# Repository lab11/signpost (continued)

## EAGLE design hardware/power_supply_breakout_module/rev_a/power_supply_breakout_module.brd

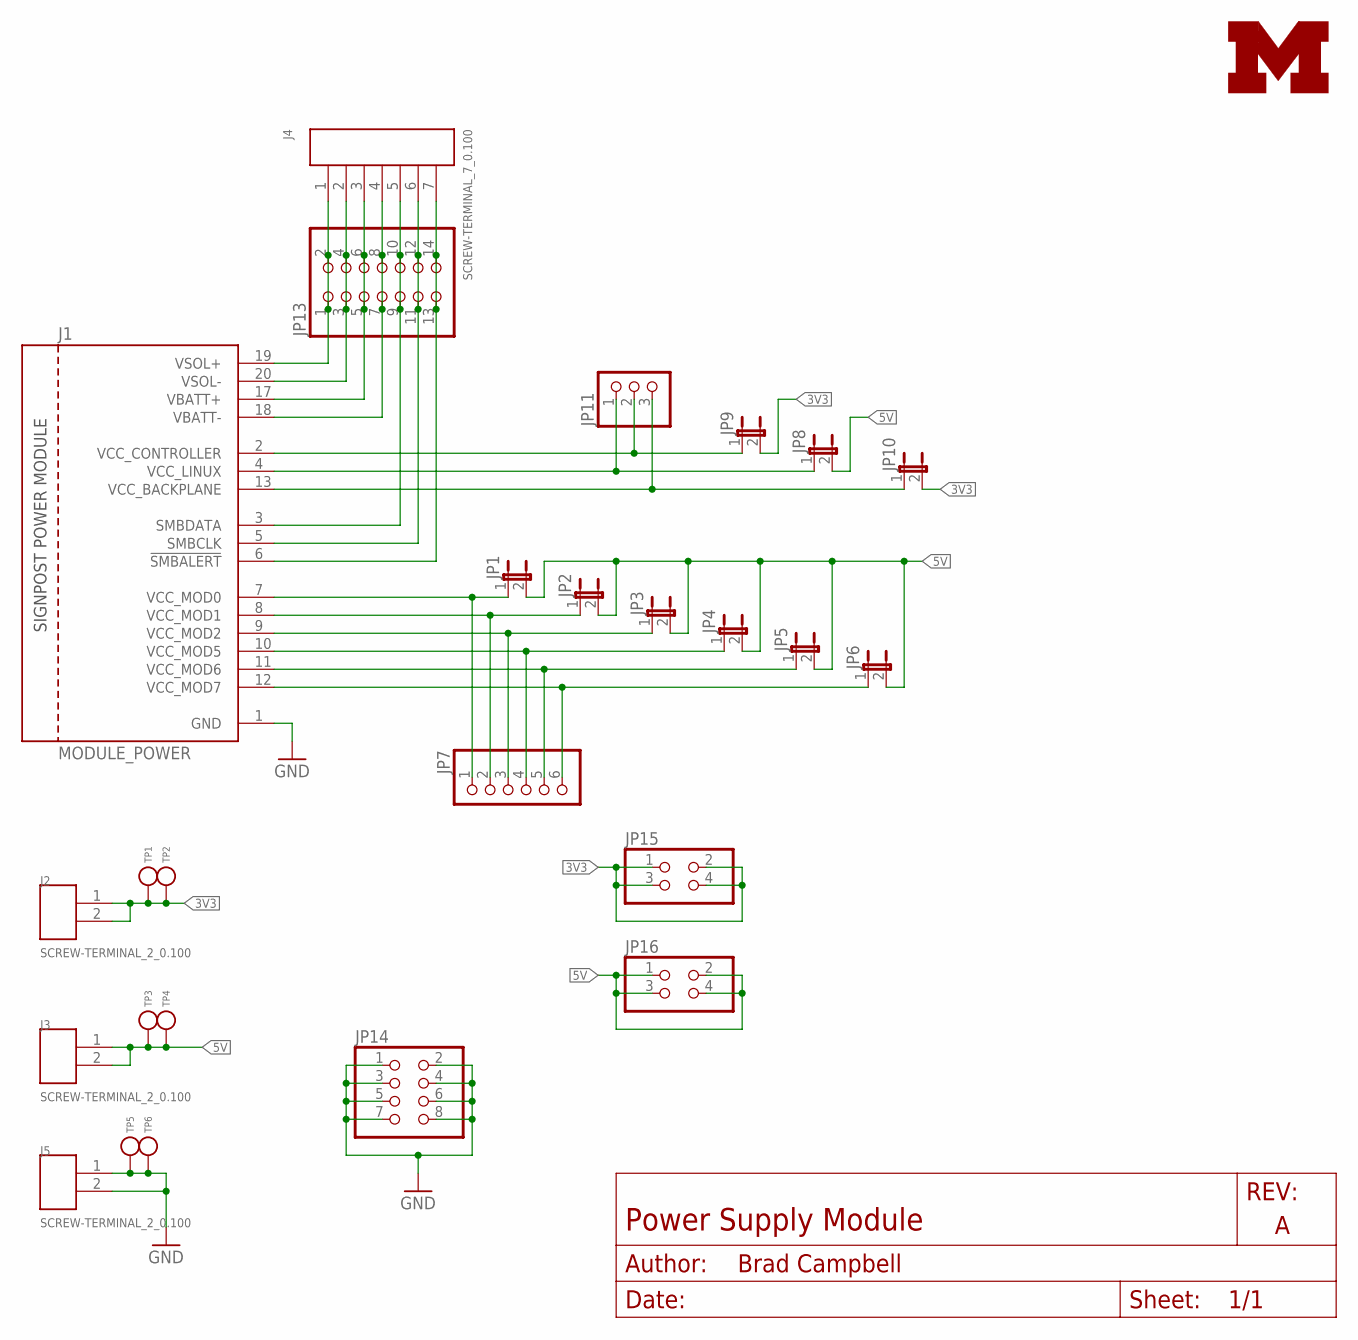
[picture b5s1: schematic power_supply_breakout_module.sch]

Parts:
J1: MODULE_POWER
J2, J3, J5: SCREW-TERMINAL_2_0.100; CONN_BLOCK_2
J4: SCREW-TERMINAL_7_0.100; CONN_BLOCK_7
JP1, JP2, JP3, JP4, JP5, JP6, JP8, JP9, JP10: JUMPER-2PTH; 1X02
JP7: PINHD-1X6; 1X06
JP11: PINHD-1X3; 1X03
JP13: PINHD-2X7; 2X07
JP14: PINHD-2X4; 2X04
JP15, JP16: PINHD-2X2; 2X02
LOGO1: UMICH_SOLID_MEDIUM; UMICH_SOLID_200MIL
TP1, TP2, TP3, TP4, TP5, TP6: TEST_POINT_0.040IN; TESTPOINT_0.040IN

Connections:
3V3: J2.1, J2.2, JP9.2, JP10.2, JP15.1, JP15.2, JP15.3, JP15.4, TP1.TESTPOINT, TP2.TESTPOINT
5V: J3.1, J3.2, JP1.2, JP2.2, JP3.2, JP4.2, JP5.2, JP6.2, JP8.2, JP16.1, JP16.2, JP16.3, JP16.4, TP3.TESTPOINT, TP4.TESTPOINT
!SMBALERT: J1.6 (!SMBALERT), J4.7, JP13.13, JP13.14
GND: J1.1 (GND), J5.1, J5.2, JP14.1, JP14.2, JP14.3, JP14.4, JP14.5, JP14.6, JP14.7, JP14.8, TP5.TESTPOINT, TP6.TESTPOINT
SMBCLK: J1.5 (SMBCLK), J4.6, JP13.11, JP13.12
SMBDATA: J1.3 (SMBDATA), J4.5, JP13.9, JP13.10
VBATT+: J1.17 (VBATT+), J4.3, JP13.5, JP13.6
VBATT-: J1.18 (VBATT-), J4.4, JP13.7, JP13.8
VCC_BACKPLANE: J1.13 (VCC_BACKPLANE), JP10.1, JP11.3
VCC_CONTROLLER: J1.2 (VCC_CONTROLLER), JP9.1, JP11.2
VCC_LINUX: J1.4 (VCC_LINUX), JP8.1, JP11.1
VCC_MOD0: J1.7 (VCC_MOD0), JP1.1, JP7.1
VCC_MOD1: J1.8 (VCC_MOD1), JP2.1, JP7.2
VCC_MOD2: J1.9 (VCC_MOD2), JP3.1, JP7.3
VCC_MOD5: J1.10 (VCC_MOD5), JP4.1, JP7.4
VCC_MOD6: J1.11 (VCC_MOD6), JP5.1, JP7.5
VCC_MOD7: J1.12 (VCC_MOD7), JP6.1, JP7.6
VSOL+: J1.19 (VSOL+), J4.1, JP13.1, JP13.2
VSOL-: J1.20 (VSOL-), J4.2, JP13.3, JP13.4

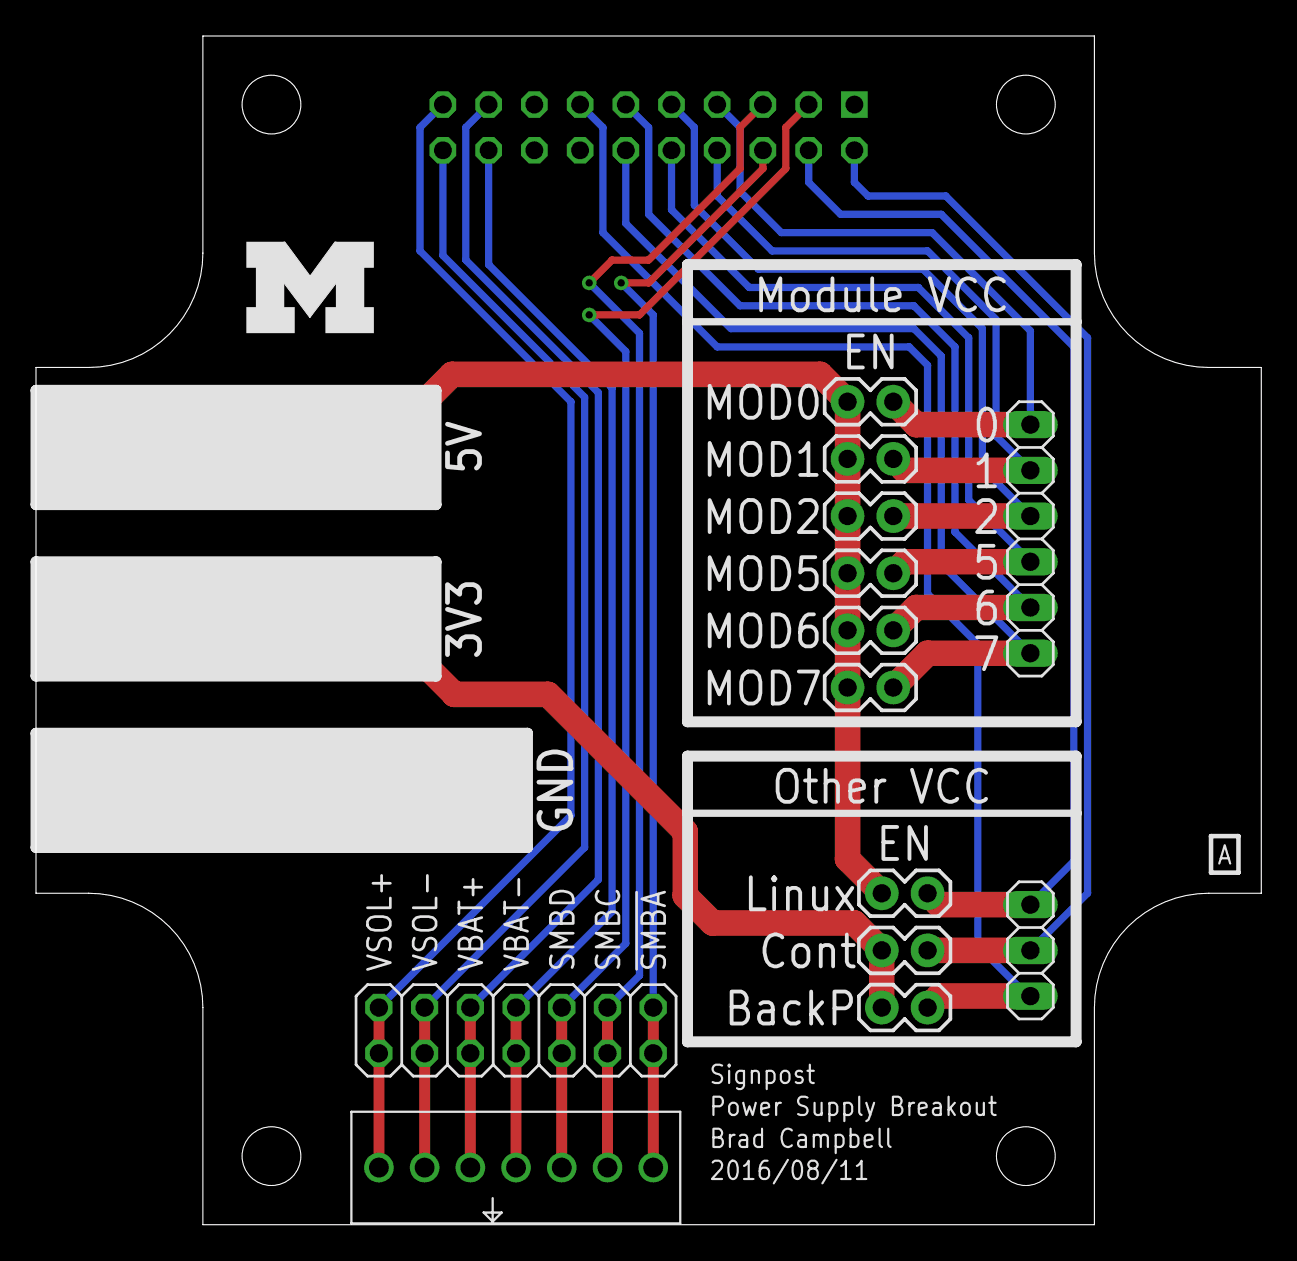
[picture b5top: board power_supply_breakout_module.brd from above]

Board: 2 copper layers, 68.1 x 66.0 mm, 27 parts (0 on the bottom side), 19 nets.

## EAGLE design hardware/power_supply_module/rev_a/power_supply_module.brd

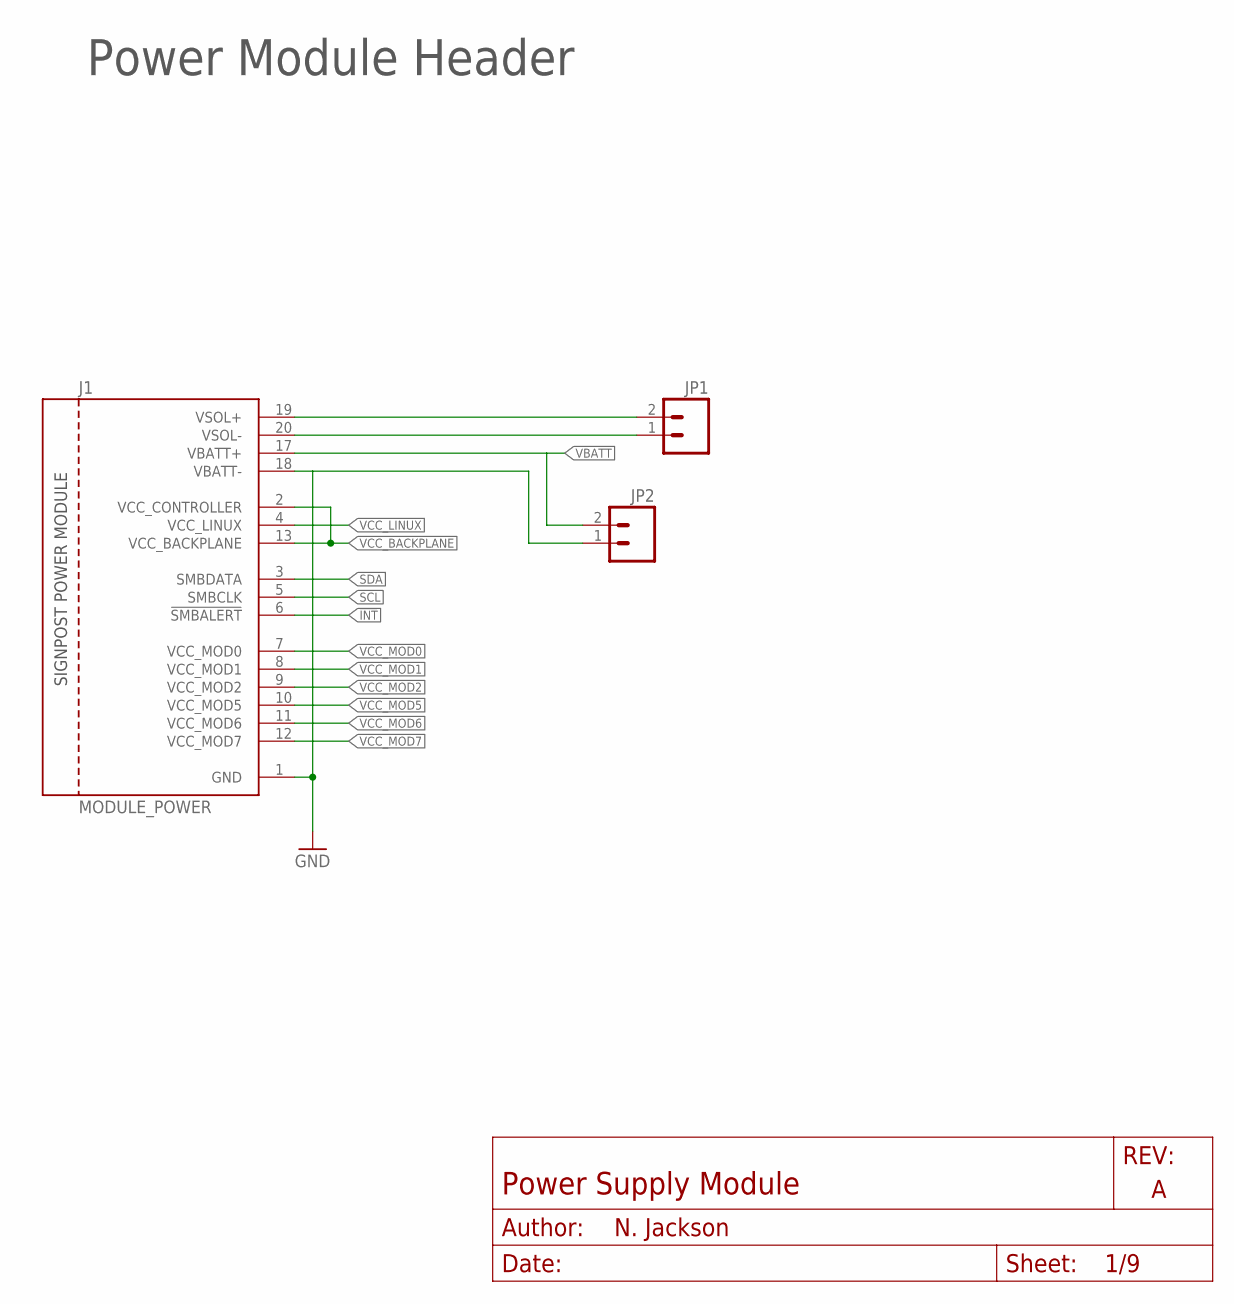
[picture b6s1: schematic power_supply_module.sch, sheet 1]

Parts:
J1: MODULE_POWER
JP1, JP2: M02PTH; 1X02

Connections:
!INT: J1.6 (!SMBALERT); also elsewhere on the board
GND: J1.1 (GND), J1.18 (VBATT-), JP2.1; also elsewhere on the board
SCL: J1.5 (SMBCLK); also elsewhere on the board
SDA: J1.3 (SMBDATA); also elsewhere on the board
VBATT: J1.17 (VBATT+), JP2.2; also elsewhere on the board
VCC_BACKPLANE: J1.2 (VCC_CONTROLLER), J1.13 (VCC_BACKPLANE); also elsewhere on the board
VCC_LINUX: J1.4 (VCC_LINUX); also elsewhere on the board
VCC_MOD0: J1.7 (VCC_MOD0); also elsewhere on the board
VCC_MOD1: J1.8 (VCC_MOD1); also elsewhere on the board
VCC_MOD2: J1.9 (VCC_MOD2); also elsewhere on the board
VCC_MOD5: J1.10 (VCC_MOD5); also elsewhere on the board
VCC_MOD6: J1.11 (VCC_MOD6); also elsewhere on the board
VCC_MOD7: J1.12 (VCC_MOD7); also elsewhere on the board
VSOL+: J1.19 (VSOL+), JP1.2; also elsewhere on the board
VSOL-: J1.20 (VSOL-), JP1.1; also elsewhere on the board

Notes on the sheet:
Power Module Header

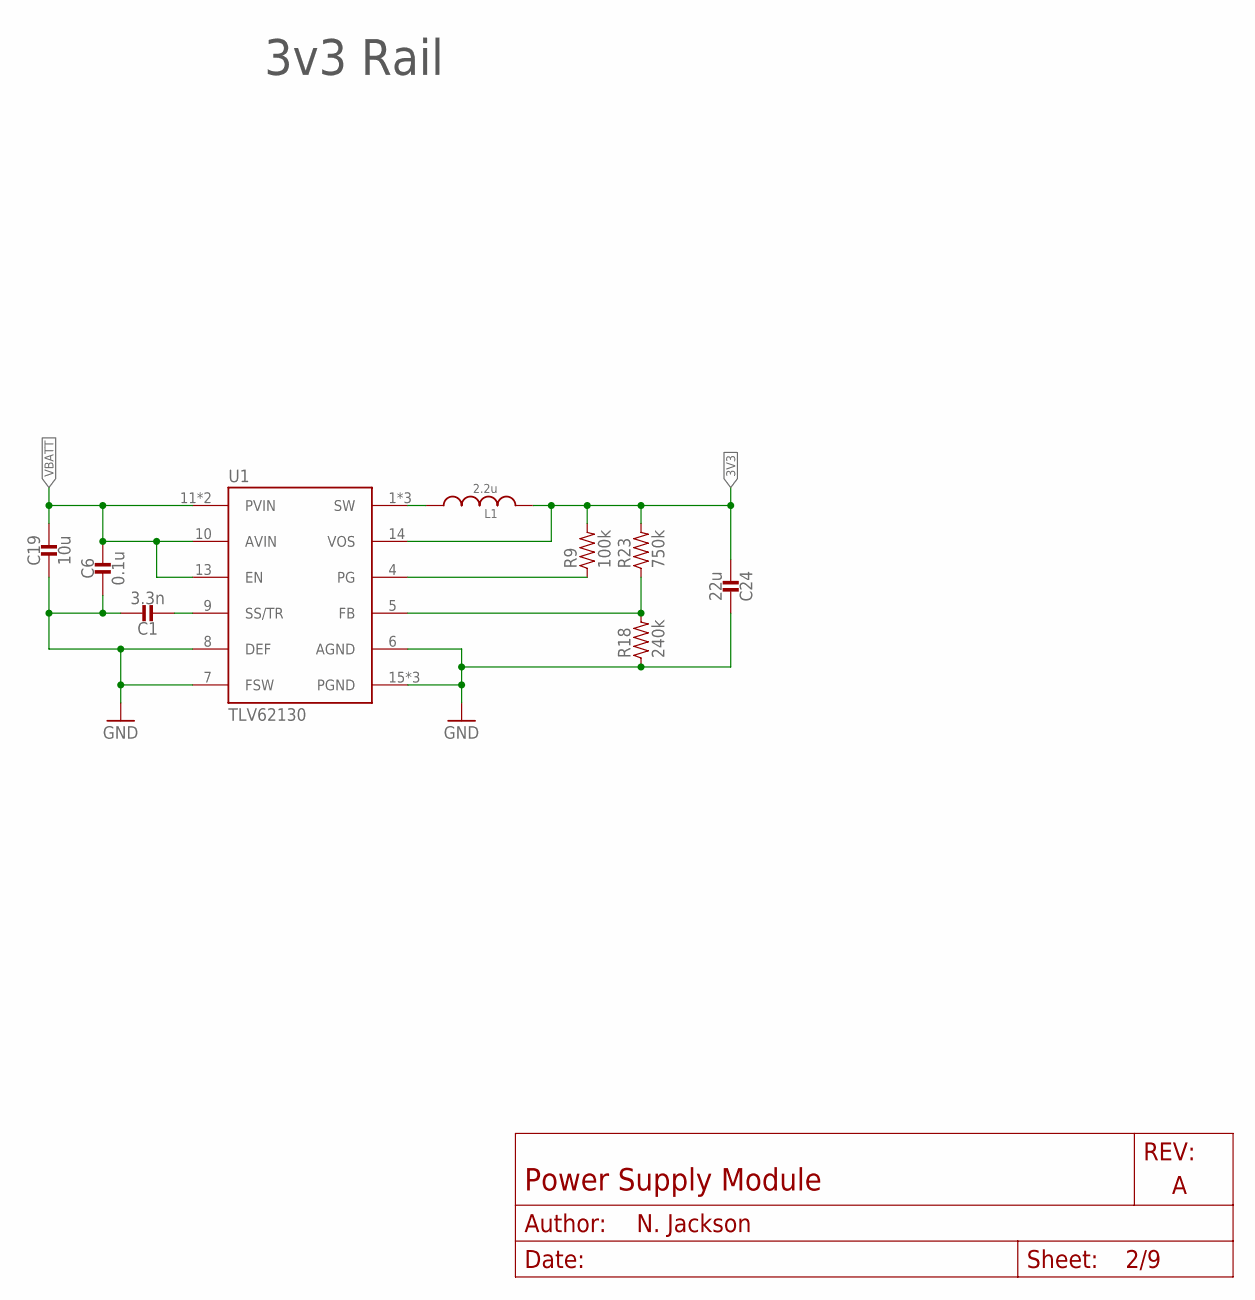
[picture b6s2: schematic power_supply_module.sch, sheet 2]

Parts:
C1: 3.3n; 0402_CAP
C6: 0.1u; 0402_CAP
C19: 10u; 0805_CAP
C24: 22u; 0603_CAP
L1: 2.2u; IHL-1212BZ-11
R9: 100k; 0402_RES
R18: 240k; 0402_RES
R23: 750k; 0402_RES
U1: TLV62130; TQFN-16/3MM

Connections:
3V3: C24.2, L1.P$2 (2), R9.2, R23.2, U1.14 (VOS); also elsewhere on the board
GND: C1.1, C6.2, C19.P$2 (2), C24.1, R18.1, U1.6 (AGND), U1.7 (FSW), U1.8 (DEF), U1.15 (PGND), U1.16 (PGND), U1.GND; also elsewhere on the board
unnamed: C1.2, U1.9 (SS/TR)
unnamed: L1.P$1 (1), U1.1 (SW), U1.2 (SW), U1.3 (SW)
unnamed: R9.1, U1.4 (PG)
unnamed: R18.2, R23.1, U1.5 (FB)
VBATT: C6.1, C19.P$1 (1), U1.10 (AVIN), U1.11 (PVIN), U1.12 (PVIN), U1.13 (EN); also elsewhere on the board

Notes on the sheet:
3v3 Rail

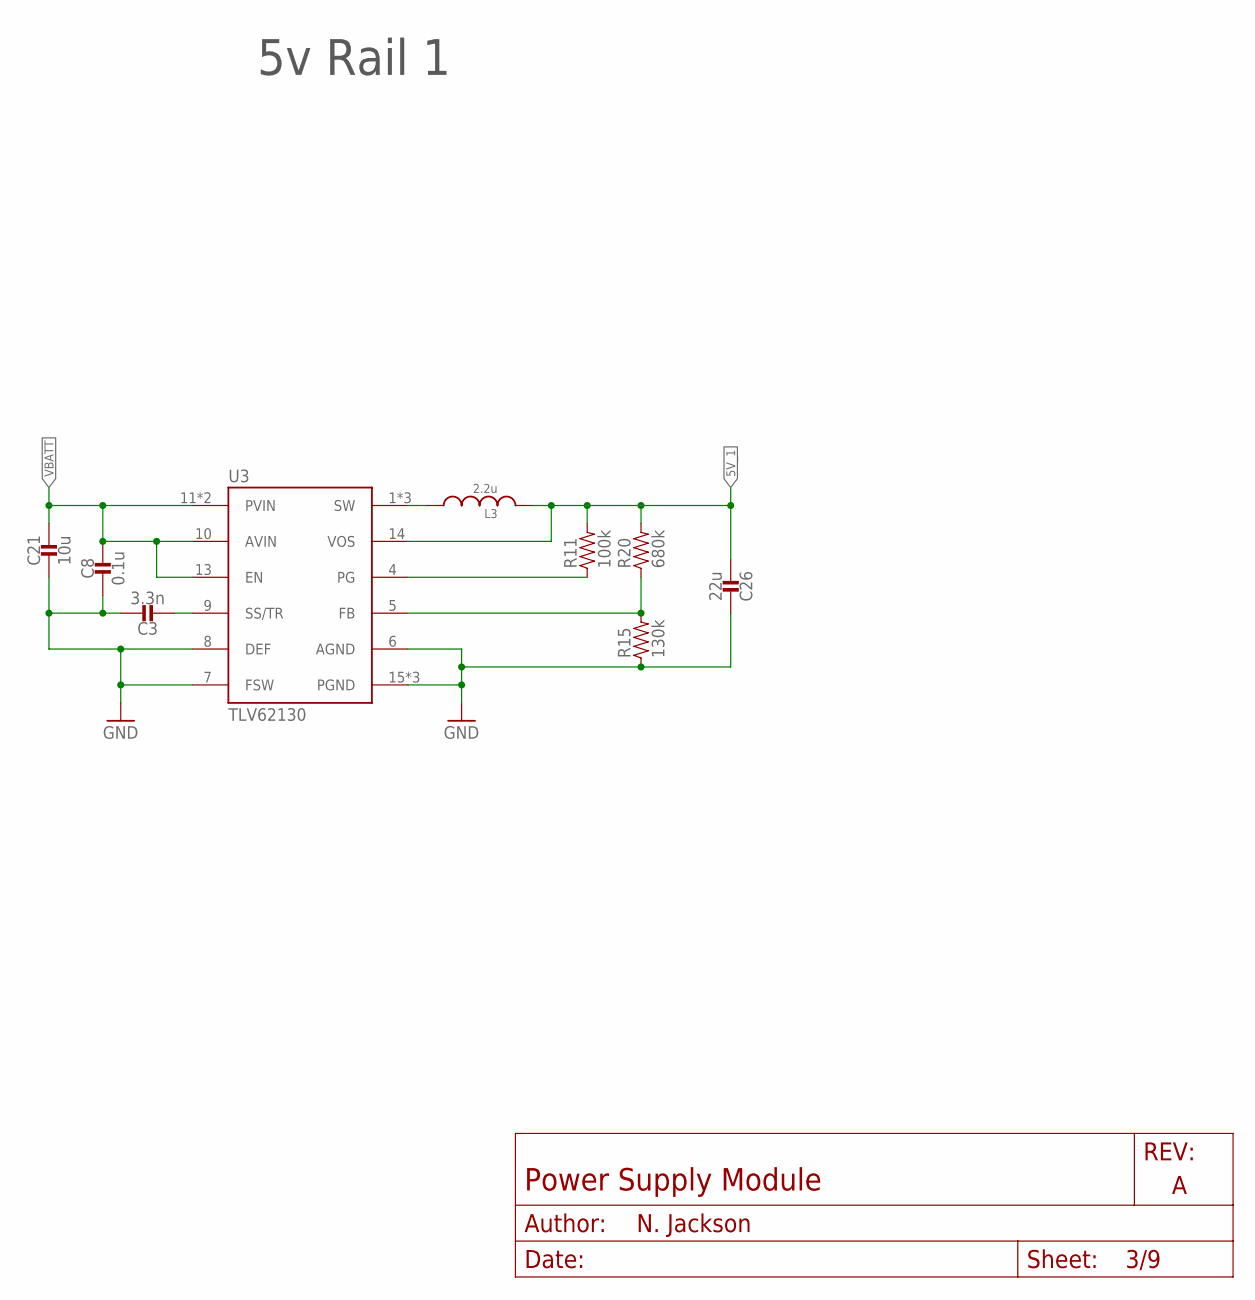
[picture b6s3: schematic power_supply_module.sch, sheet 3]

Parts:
C3: 3.3n; 0402_CAP
C8: 0.1u; 0402_CAP
C21: 10u; 0805_CAP
C26: 22u; 0603_CAP
L3: 2.2u; IHL-1212BZ-11
R11: 100k; 0402_RES
R15: 130k; 0402_RES
R20: 680k; 0402_RES
U3: TLV62130; TQFN-16/3MM

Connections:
5V_1: C26.2, L3.P$2 (2), R11.2, R20.2, U3.14 (VOS); also elsewhere on the board
GND: C3.1, C8.2, C21.P$2 (2), C26.1, R15.1, U3.6 (AGND), U3.7 (FSW), U3.8 (DEF), U3.15 (PGND), U3.16 (PGND), U3.GND; also elsewhere on the board
unnamed: C3.2, U3.9 (SS/TR)
unnamed: L3.P$1 (1), U3.1 (SW), U3.2 (SW), U3.3 (SW)
unnamed: R11.1, U3.4 (PG)
unnamed: R15.2, R20.1, U3.5 (FB)
VBATT: C8.1, C21.P$1 (1), U3.10 (AVIN), U3.11 (PVIN), U3.12 (PVIN), U3.13 (EN); also elsewhere on the board

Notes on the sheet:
5v Rail 1

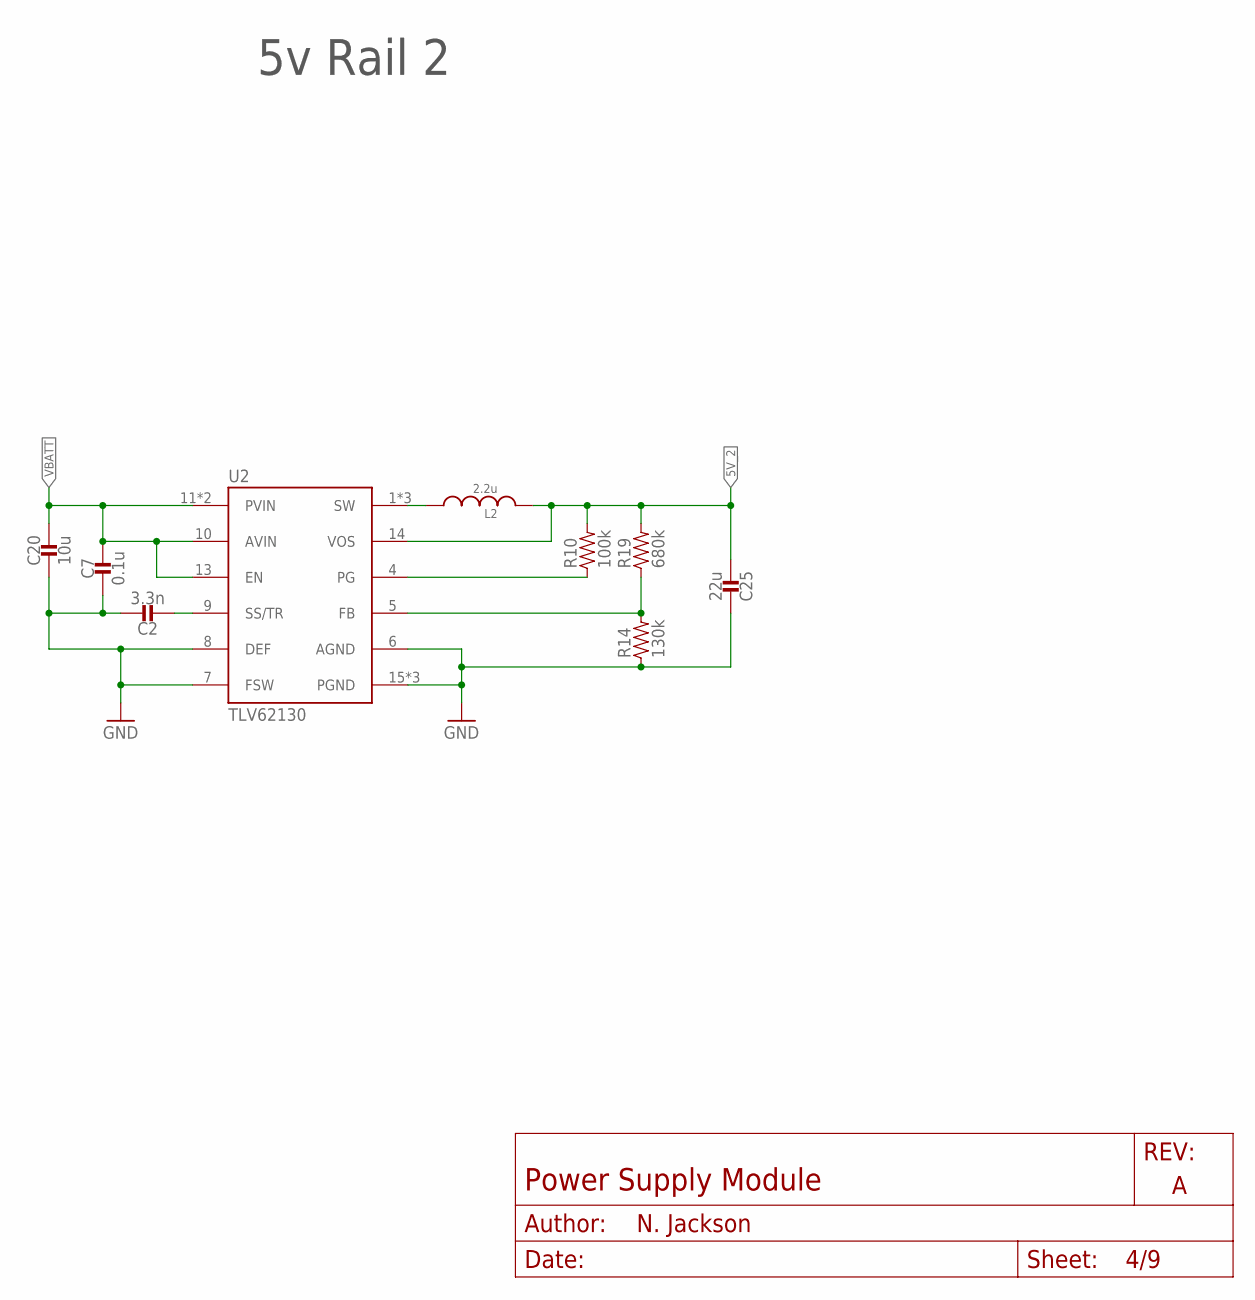
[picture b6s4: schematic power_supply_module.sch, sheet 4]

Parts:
C2: 3.3n; 0402_CAP
C7: 0.1u; 0402_CAP
C20: 10u; 0805_CAP
C25: 22u; 0603_CAP
L2: 2.2u; IHL-1212BZ-11
R10: 100k; 0402_RES
R14: 130k; 0402_RES
R19: 680k; 0402_RES
U2: TLV62130; TQFN-16/3MM

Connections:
5V_2: C25.2, L2.P$2 (2), R10.2, R19.2, U2.14 (VOS); also elsewhere on the board
GND: C2.1, C7.2, C20.P$2 (2), C25.1, R14.1, U2.6 (AGND), U2.7 (FSW), U2.8 (DEF), U2.15 (PGND), U2.16 (PGND), U2.GND; also elsewhere on the board
unnamed: C2.2, U2.9 (SS/TR)
unnamed: L2.P$1 (1), U2.1 (SW), U2.2 (SW), U2.3 (SW)
unnamed: R10.1, U2.4 (PG)
unnamed: R14.2, R19.1, U2.5 (FB)
VBATT: C7.1, C20.P$1 (1), U2.10 (AVIN), U2.11 (PVIN), U2.12 (PVIN), U2.13 (EN); also elsewhere on the board

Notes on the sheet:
5v Rail 2

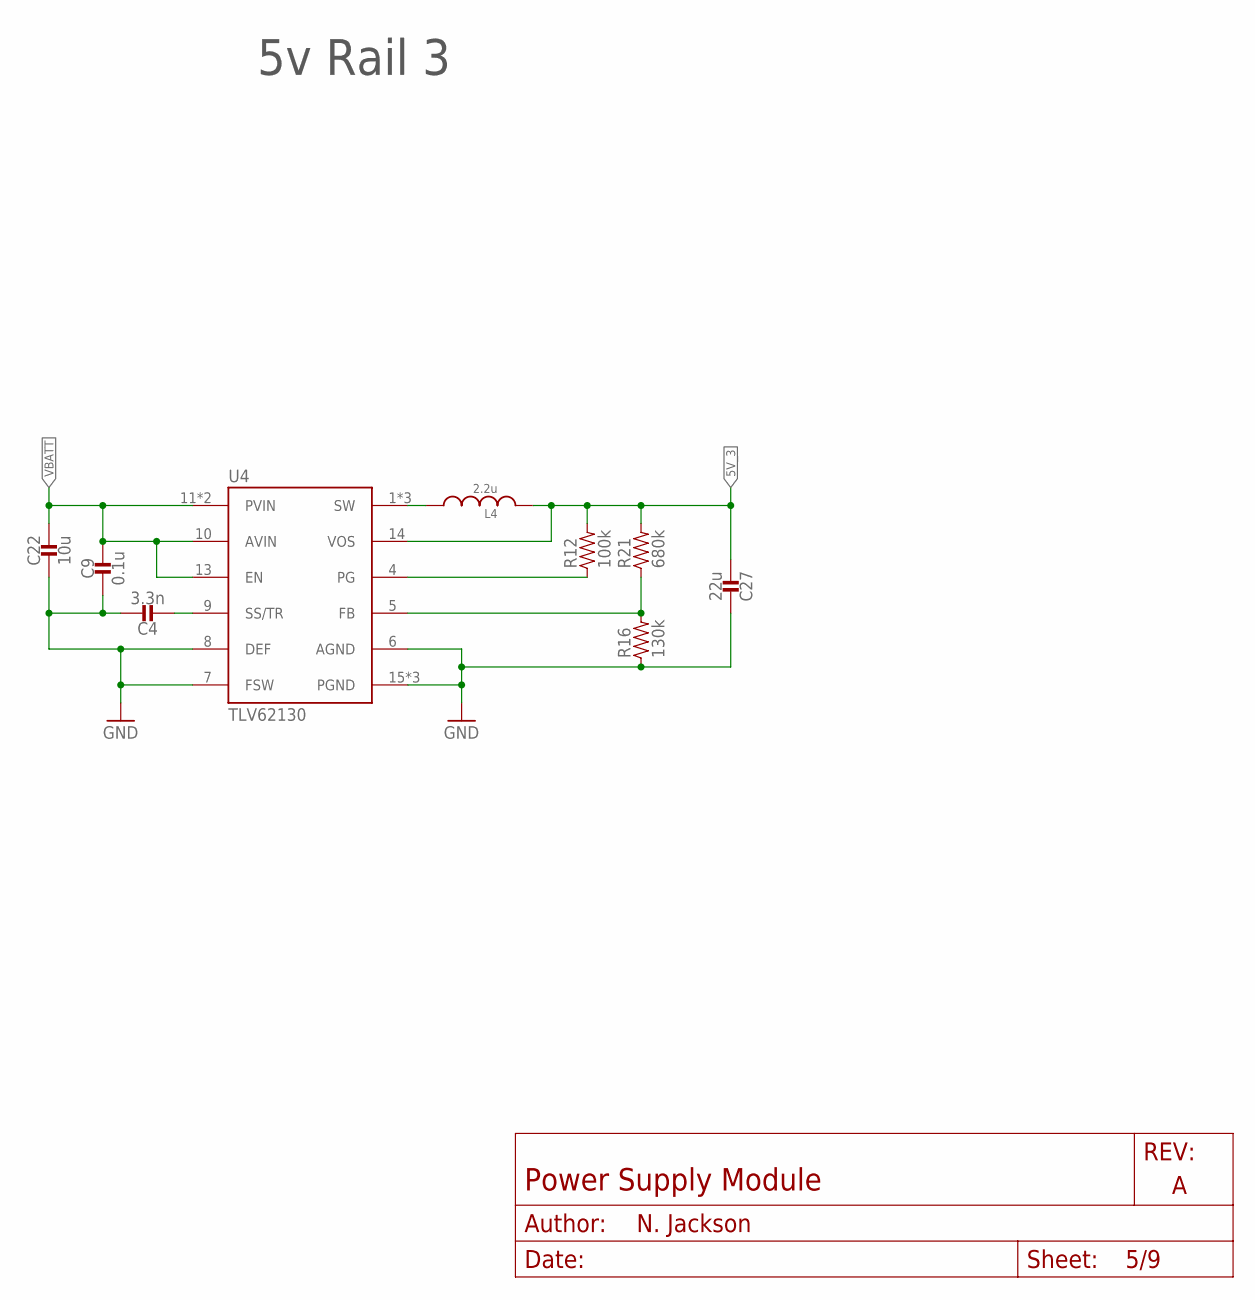
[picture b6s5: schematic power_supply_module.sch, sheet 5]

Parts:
C4: 3.3n; 0402_CAP
C9: 0.1u; 0402_CAP
C22: 10u; 0805_CAP
C27: 22u; 0603_CAP
L4: 2.2u; IHL-1212BZ-11
R12: 100k; 0402_RES
R16: 130k; 0402_RES
R21: 680k; 0402_RES
U4: TLV62130; TQFN-16/3MM

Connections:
5V_3: C27.2, L4.P$2 (2), R12.2, R21.2, U4.14 (VOS); also elsewhere on the board
GND: C4.1, C9.2, C22.P$2 (2), C27.1, R16.1, U4.6 (AGND), U4.7 (FSW), U4.8 (DEF), U4.15 (PGND), U4.16 (PGND), U4.GND; also elsewhere on the board
unnamed: C4.2, U4.9 (SS/TR)
unnamed: L4.P$1 (1), U4.1 (SW), U4.2 (SW), U4.3 (SW)
unnamed: R12.1, U4.4 (PG)
unnamed: R16.2, R21.1, U4.5 (FB)
VBATT: C9.1, C22.P$1 (1), U4.10 (AVIN), U4.11 (PVIN), U4.12 (PVIN), U4.13 (EN); also elsewhere on the board

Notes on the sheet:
5v Rail 3

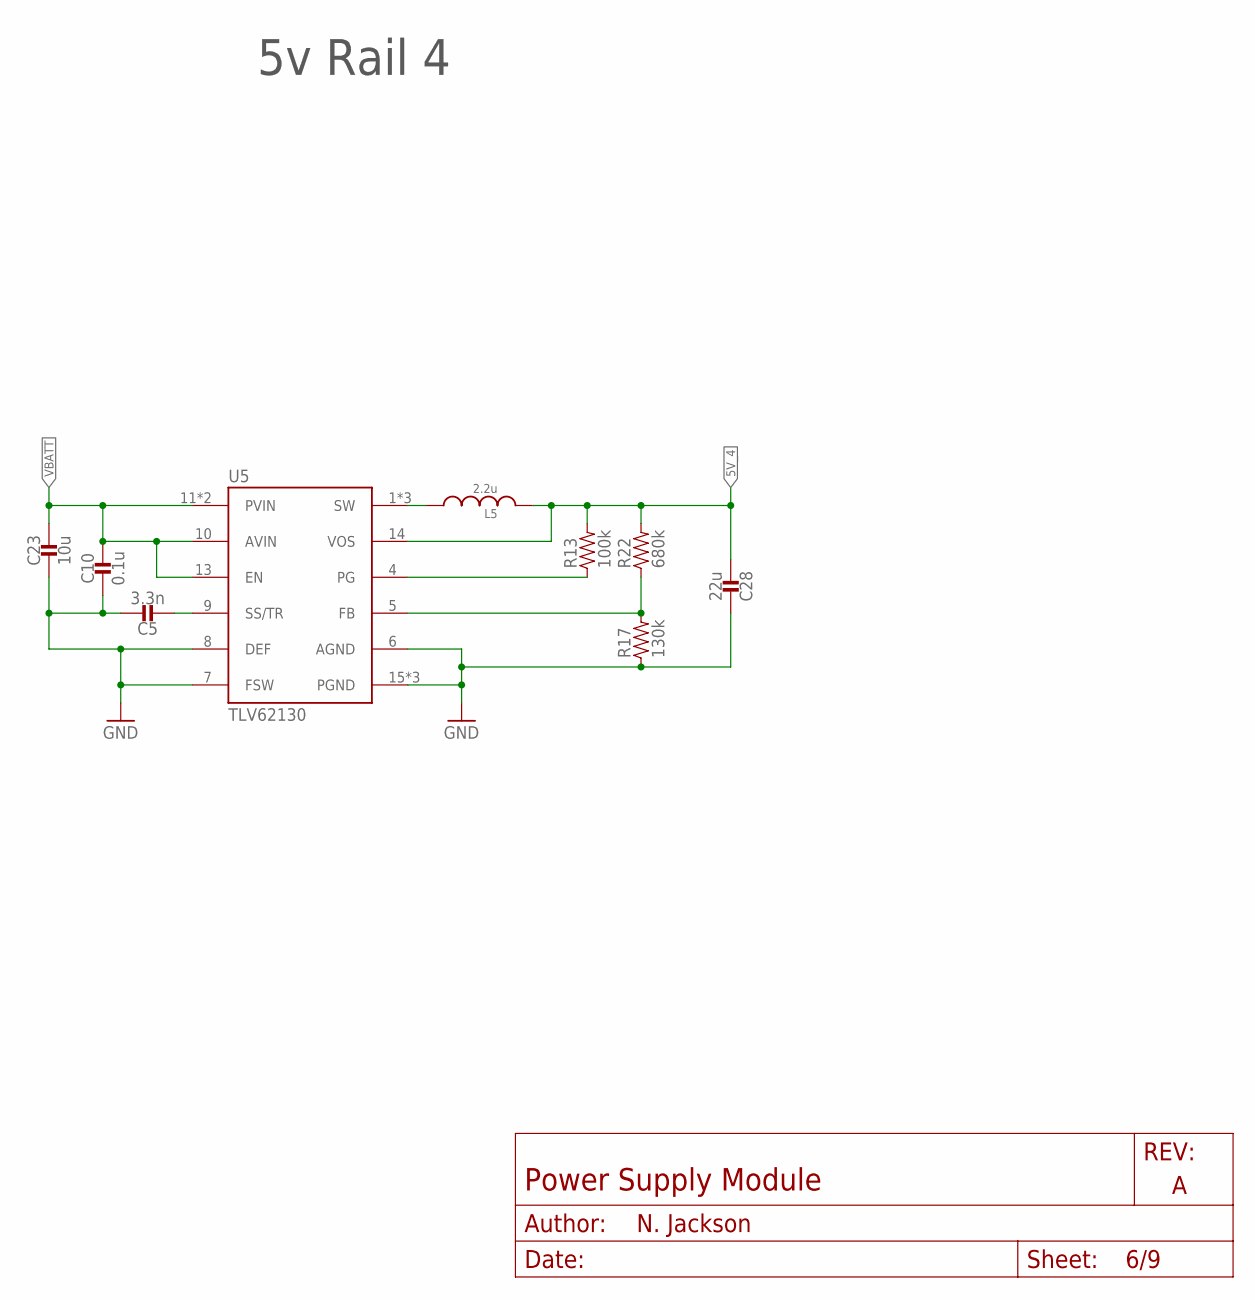
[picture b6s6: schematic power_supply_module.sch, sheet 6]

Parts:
C5: 3.3n; 0402_CAP
C10: 0.1u; 0402_CAP
C23: 10u; 0805_CAP
C28: 22u; 0603_CAP
L5: 2.2u; IHL-1212BZ-11
R13: 100k; 0402_RES
R17: 130k; 0402_RES
R22: 680k; 0402_RES
U5: TLV62130; TQFN-16/3MM

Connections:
5V_4: C28.2, L5.P$2 (2), R13.2, R22.2, U5.14 (VOS); also elsewhere on the board
GND: C5.1, C10.2, C23.P$2 (2), C28.1, R17.1, U5.6 (AGND), U5.7 (FSW), U5.8 (DEF), U5.15 (PGND), U5.16 (PGND), U5.GND; also elsewhere on the board
unnamed: C5.2, U5.9 (SS/TR)
unnamed: L5.P$1 (1), U5.1 (SW), U5.2 (SW), U5.3 (SW)
unnamed: R13.1, U5.4 (PG)
unnamed: R17.2, R22.1, U5.5 (FB)
VBATT: C10.1, C23.P$1 (1), U5.10 (AVIN), U5.11 (PVIN), U5.12 (PVIN), U5.13 (EN); also elsewhere on the board

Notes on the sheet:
5v Rail 4

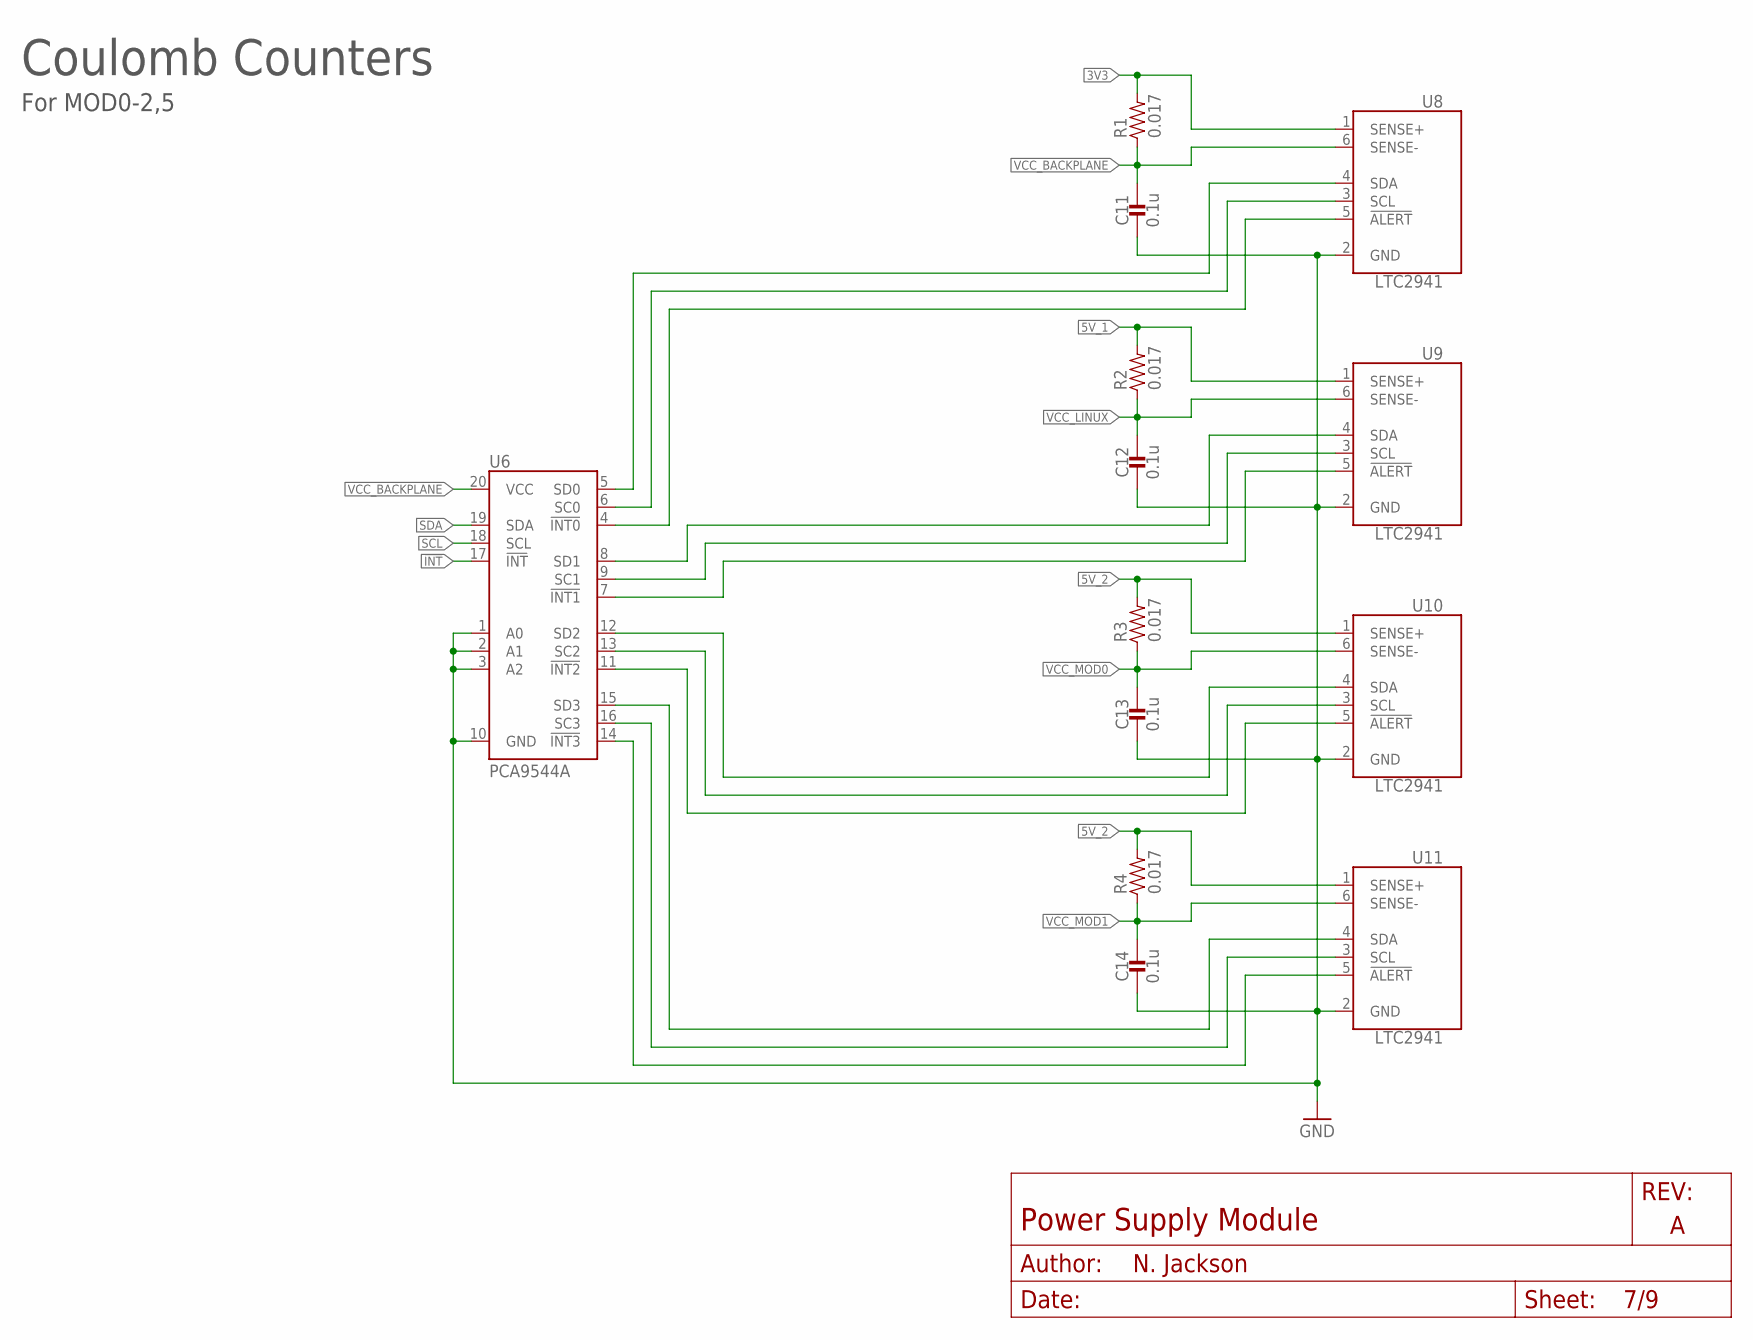
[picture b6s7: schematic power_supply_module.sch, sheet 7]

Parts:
C11, C12, C13, C14: 0.1u; 0402_CAP
R1, R2, R3, R4: 0.017; 0805_RES
U6: PCA9544A; SO20L
U8, U9, U10, U11: LTC2941; DFN-6-2MMX3MM

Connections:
3V3: R1.2, U8.1 (SENSE+); also elsewhere on the board
5V_1: R2.2, U9.1 (SENSE+); also elsewhere on the board
5V_2: R3.2, R4.2, U10.1 (SENSE+), U11.1 (SENSE+); also elsewhere on the board
!INT: U6.17 (!INT); also elsewhere on the board
GND: C11.2, C12.2, C13.2, C14.2, U6.1 (A0), U6.2 (A1), U6.3 (A2), U6.10 (GND), U8.2 (GND), U9.2 (GND), U10.2 (GND), U11.2 (GND); also elsewhere on the board
unnamed: U6.5 (SD0), U8.4 (SDA)
unnamed: U6.6 (SC0), U8.3 (SCL)
unnamed: U6.12 (SD2), U10.4 (SDA)
unnamed: U6.13 (SC2), U10.3 (SCL)
unnamed: U6.11 (!INT2), U10.5 (!ALERT)
unnamed: U6.15 (SD3), U11.4 (SDA)
unnamed: U6.16 (SC3), U11.3 (SCL)
unnamed: U6.14 (!INT3), U11.5 (!ALERT)
unnamed: U6.4 (!INT0), U8.5 (!ALERT)
unnamed: U6.8 (SD1), U9.4 (SDA)
unnamed: U6.9 (SC1), U9.3 (SCL)
unnamed: U6.7 (!INT1), U9.5 (!ALERT)
SCL: U6.18 (SCL); also elsewhere on the board
SDA: U6.19 (SDA); also elsewhere on the board
VCC_BACKPLANE: C11.1, R1.1, U6.20 (VCC), U8.6 (SENSE-); also elsewhere on the board
VCC_LINUX: C12.1, R2.1, U9.6 (SENSE-); also elsewhere on the board
VCC_MOD0: C13.1, R3.1, U10.6 (SENSE-); also elsewhere on the board
VCC_MOD1: C14.1, R4.1, U11.6 (SENSE-); also elsewhere on the board

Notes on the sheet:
Coulomb Counters
For MOD0-2,5
